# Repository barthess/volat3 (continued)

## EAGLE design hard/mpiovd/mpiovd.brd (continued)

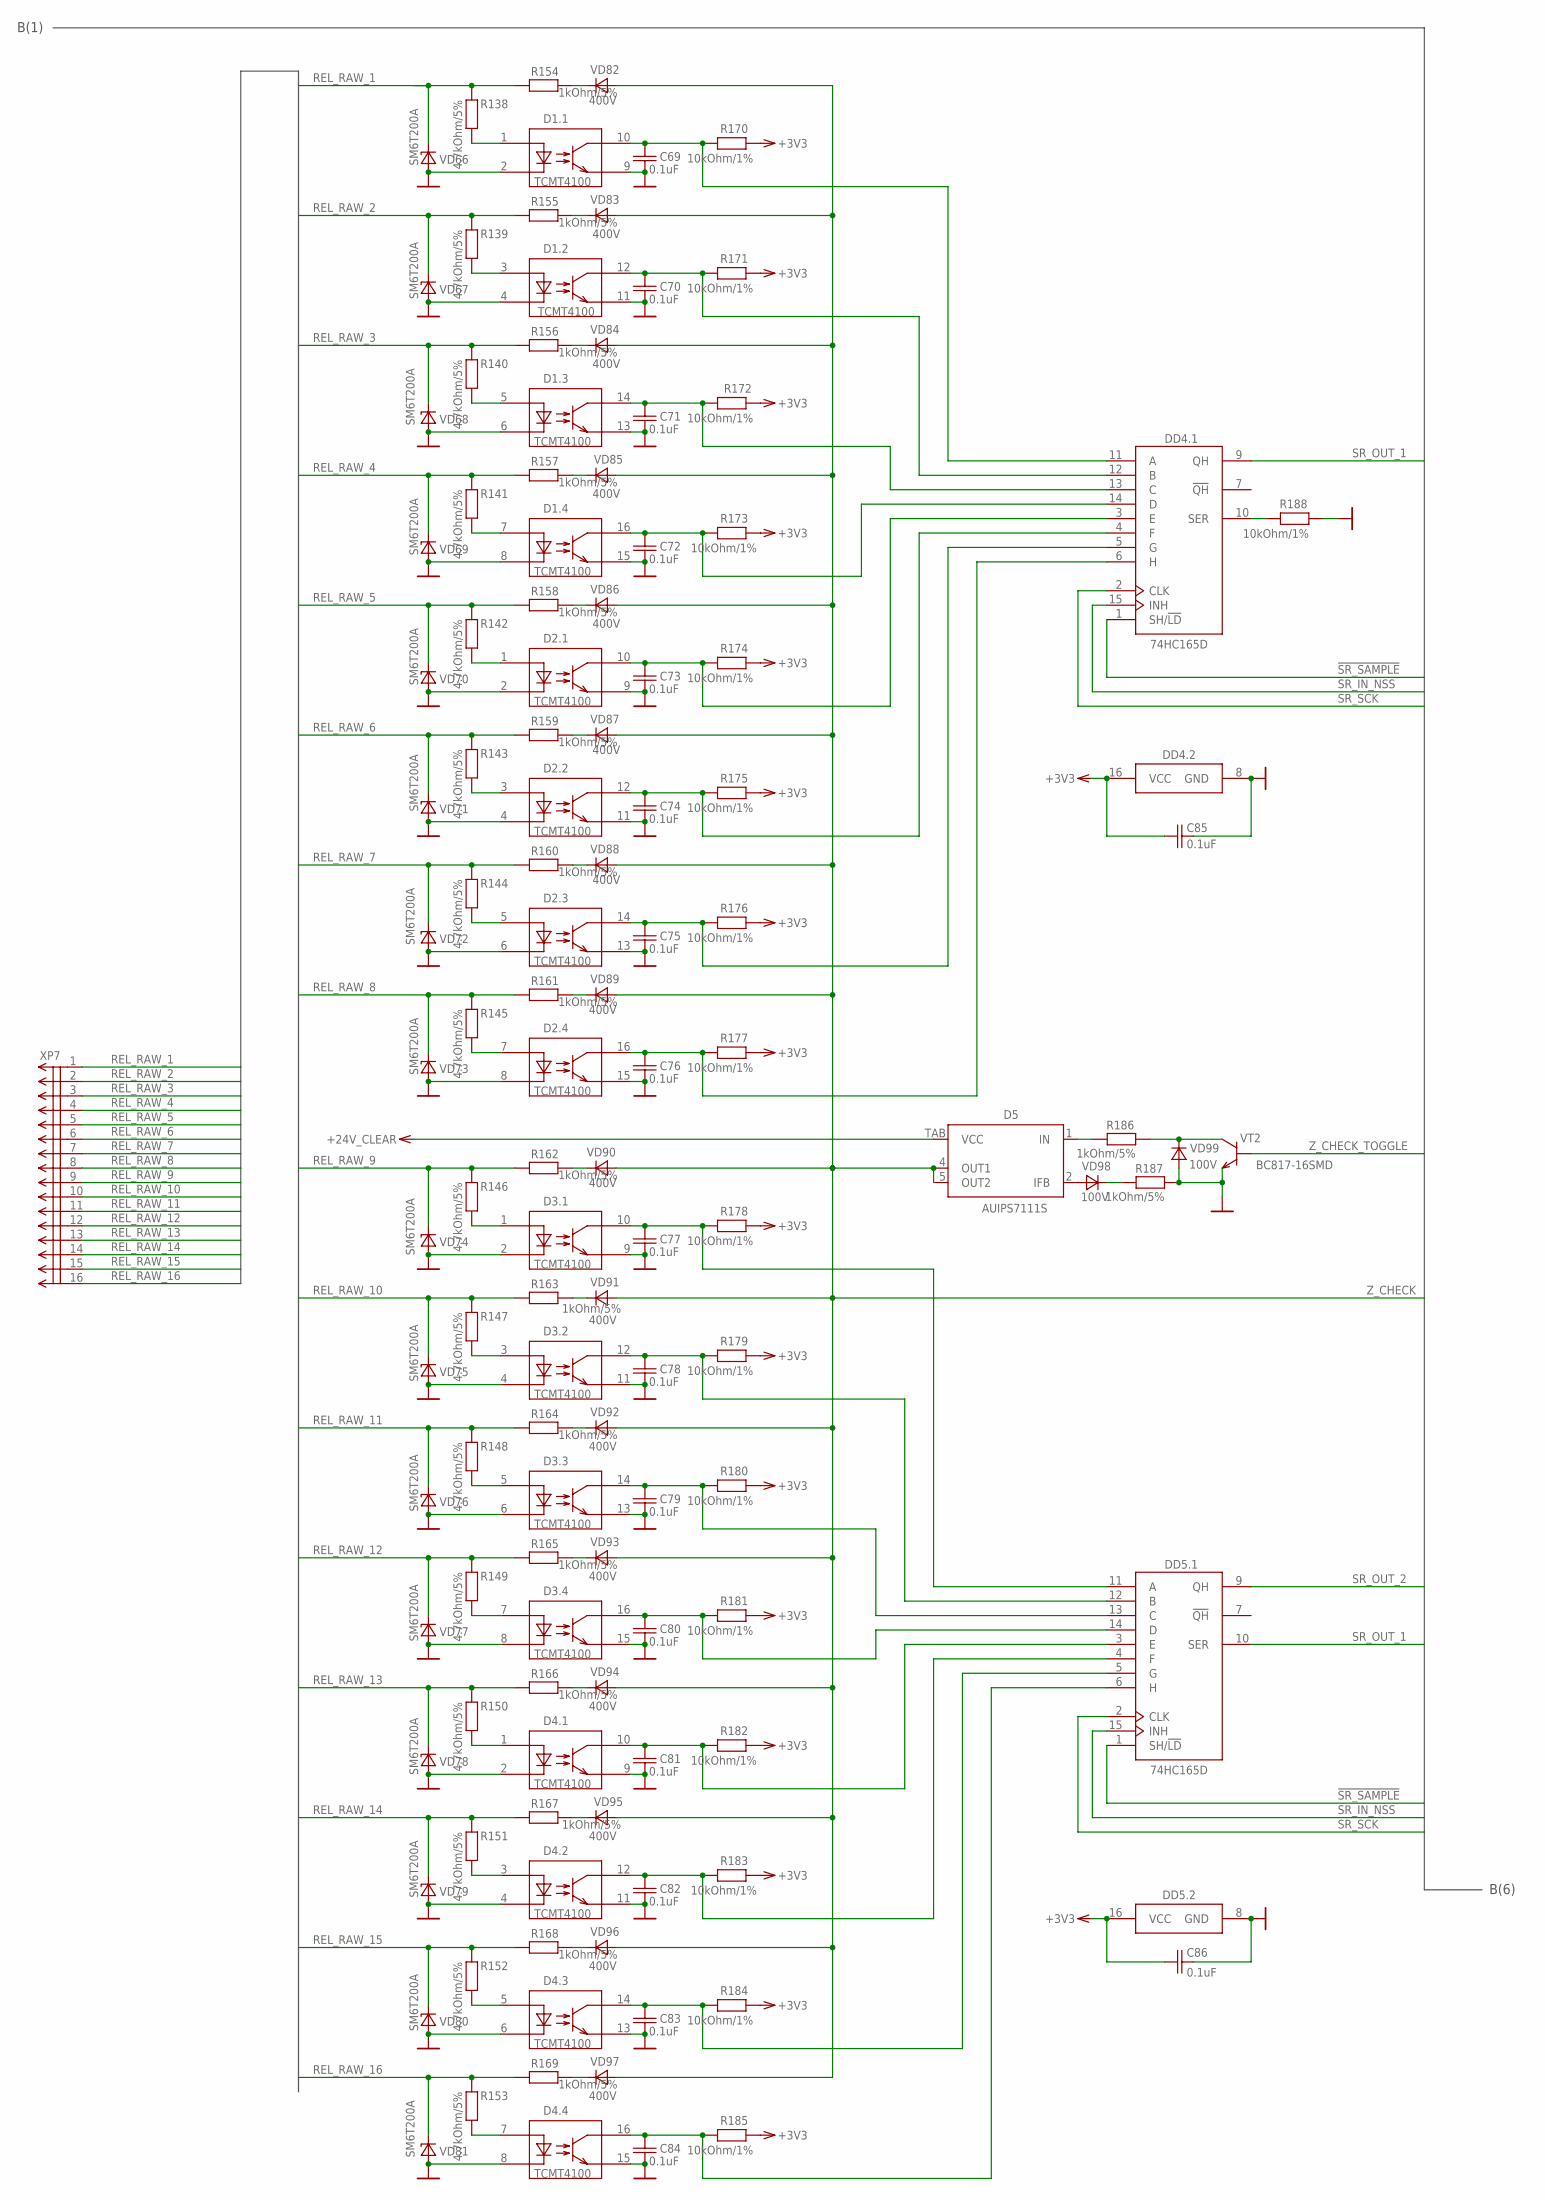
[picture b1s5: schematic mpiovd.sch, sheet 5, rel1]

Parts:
C69, C70, C71, C72, C73, C74, C75, C76, C77, C78, C79, C80, C81, C82, C83, C84, C85, C86: 0.1uF; C0603; PARTNO C0603C104K5RACTU
D1, D2, D3, D4: TCMT4100; SO16; PARTNO TCMT4100
D5: AUIPS7111S; TO252-5-11; PARTNO AUIPS7111S
DD4, DD5: 74HC165D; SO16; PARTNO IN74HC165AD
R138, R139, R140, R141, R142, R143, R144, R145, R146, R147, R148, R149, R150, R151, R152, R153: 4.7kOhm/5%; R1206; PARTNO RC1206JR-074K7L
R154, R155, R156, R157, R158, R159, R160, R161, R162, R163, R164, R165, R166, R167, R168, R169: 1kOhm/5%; R2512; PARTNO RC2512JK-071KL
R170, R171, R172, R173, R174, R175, R176, R177, R178, R179, R180, R181, R182, R183, R184, R185, R188: 10kOhm/1%; R0603; PARTNO RC0603FR-1010KL
R186, R187: 1kOhm/5%; R0805; PARTNO ERJ6GEYJ102V
VD66, VD67, VD68, VD69, VD70, VD71, VD72, VD73, VD74, VD75, VD76, VD77, VD78, VD79, VD80, VD81: SM6T200A; SMB; PARTNO SM6T200A
VD82, VD83, VD84, VD85, VD86, VD87, VD88, VD89, VD90, VD91, VD92, VD93, VD94, VD95, VD96, VD97: 400V; SMA; PARTNO S1G-E3/61T
VD98, VD99: 100V; SOD323; PARTNO 1N4148WS-V-GS18
VT2: BC817-16SMD; SOT23-BEC; PARTNO BC817
XP7: MOLEX-90130-16; PARTNO 90130-1216

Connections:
!SR_SAMPLE: DD4.1 (SH/!LD), DD5.1 (SH/!LD); also elsewhere on the board
+3V3: C85.1, C86.1, DD4.16 (VCC), DD5.16 (VCC), R170.1, R171.1, R172.1, R173.1, R174.1, R175.1, R176.1, R177.1, R178.1, R179.1, R180.1, R181.1, R182.1, R183.1, R184.1, R185.1; also elsewhere on the board
+24V_CLEAR: D5.TAB (VCC); also elsewhere on the board
DISCRETE_1: C69.1, D1.10 (TC), DD4.11 (A), R170.2
DISCRETE_2: C70.1, D1.12 (TC), DD4.12 (B), R171.2
DISCRETE_3: C71.1, D1.14 (TC), DD4.13 (C), R172.2
DISCRETE_4: C72.1, D1.16 (TC), DD4.14 (D), R173.2
DISCRETE_5: C73.1, D2.10 (TC), DD4.3 (E), R174.2
DISCRETE_6: C74.1, D2.12 (TC), DD4.4 (F), R175.2
DISCRETE_7: C75.1, D2.14 (TC), DD4.5 (G), R176.2
DISCRETE_8: C76.1, D2.16 (TC), DD4.6 (H), R177.2
DISCRETE_9: C77.1, D3.10 (TC), DD5.11 (A), R178.2
DISCRETE_10: C78.1, D3.12 (TC), DD5.12 (B), R179.2
DISCRETE_11: C79.1, D3.14 (TC), DD5.13 (C), R180.2
DISCRETE_12: C80.1, D3.16 (TC), DD5.14 (D), R181.2
DISCRETE_13: C81.1, D4.10 (TC), DD5.3 (E), R182.2
DISCRETE_14: C82.1, D4.12 (TC), DD5.4 (F), R183.2
DISCRETE_15: C83.1, D4.14 (TC), DD5.5 (G), R184.2
DISCRETE_16: C84.1, D4.16 (TC), DD5.6 (H), R185.2
GND: C69.2, C70.2, C71.2, C72.2, C73.2, C74.2, C75.2, C76.2, C77.2, C78.2, C79.2, C80.2, C81.2, C82.2, C83.2, C84.2, C85.2, C86.2, D1.2 (DC), D1.4 (DC), D1.6 (DC), D1.8 (DC), D1.9 (TE), D1.11 (TE), D1.13 (TE), D1.15 (TE), D2.2 (DC), D2.4 (DC), D2.6 (DC), D2.8 (DC), D2.9 (TE), D2.11 (TE), D2.13 (TE), D2.15 (TE), D3.2 (DC), D3.4 (DC), D3.6 (DC), D3.8 (DC), D3.9 (TE), D3.11 (TE), D3.13 (TE), D3.15 (TE), D4.2 (DC), D4.4 (DC), D4.6 (DC), D4.8 (DC), D4.9 (TE), D4.11 (TE), D4.13 (TE), D4.15 (TE), DD4.8 (GND), DD5.8 (GND), R187.1, R188.1, VD66.A, VD67.A, VD68.A, VD69.A, VD70.A, VD71.A, VD72.A, VD73.A, VD74.A, VD75.A, VD76.A, VD77.A, VD78.A, VD79.A, VD80.A, VD81.A, VD99.A, VT2.E; also elsewhere on the board
unnamed: D5.1 (IN), R186.2
unnamed: R186.1, VD99.C, VT2.C
unnamed: D5.2 (IFB), VD98.A
unnamed: R187.2, VD98.C
unnamed: R154.2, VD82.C
unnamed: R155.2, VD83.C
unnamed: R156.2, VD84.C
unnamed: R157.2, VD85.C
unnamed: R158.2, VD86.C
unnamed: R159.2, VD87.C
unnamed: R160.2, VD88.C
unnamed: R161.2, VD89.C
unnamed: R162.2, VD90.C
unnamed: R163.2, VD91.C
unnamed: R164.2, VD92.C
unnamed: R165.2, VD93.C
unnamed: R166.2, VD94.C
unnamed: R167.2, VD95.C
unnamed: R168.2, VD96.C
unnamed: R169.2, VD97.C
unnamed: D1.1 (DA), R138.2
unnamed: D1.3 (DA), R139.2
unnamed: D1.5 (DA), R140.2
unnamed: D1.7 (DA), R141.2
unnamed: D2.1 (DA), R142.2
unnamed: D2.3 (DA), R143.2
unnamed: D2.5 (DA), R144.2
unnamed: D2.7 (DA), R145.2
unnamed: D3.1 (DA), R146.2
unnamed: D3.3 (DA), R147.2
unnamed: D3.5 (DA), R148.2
unnamed: D3.7 (DA), R149.2
unnamed: D4.1 (DA), R150.2
unnamed: D4.3 (DA), R151.2
unnamed: D4.5 (DA), R152.2
unnamed: D4.7 (DA), R153.2
unnamed: DD4.10 (SER), R188.2
REL_RAW_1: R138.1, R154.1, VD66.C, XP7.1
REL_RAW_2: R139.1, R155.1, VD67.C, XP7.2
REL_RAW_3: R140.1, R156.1, VD68.C, XP7.3
REL_RAW_4: R141.1, R157.1, VD69.C, XP7.4
REL_RAW_5: R142.1, R158.1, VD70.C, XP7.5
REL_RAW_6: R143.1, R159.1, VD71.C, XP7.6
REL_RAW_7: R144.1, R160.1, VD72.C, XP7.7
REL_RAW_8: R145.1, R161.1, VD73.C, XP7.8
REL_RAW_9: R146.1, R162.1, VD74.C, XP7.9
REL_RAW_10: R147.1, R163.1, VD75.C, XP7.10
REL_RAW_11: R148.1, R164.1, VD76.C, XP7.11
REL_RAW_12: R149.1, R165.1, VD77.C, XP7.12
REL_RAW_13: R150.1, R166.1, VD78.C, XP7.13
REL_RAW_14: R151.1, R167.1, VD79.C, XP7.14
REL_RAW_15: R152.1, R168.1, VD80.C, XP7.15
REL_RAW_16: R153.1, R169.1, VD81.C, XP7.16
SR_IN_NSS: DD4.15 (INH), DD5.15 (INH); also elsewhere on the board
SR_OUT_1: DD4.9 (QH), DD5.10 (SER)
SR_OUT_2: DD5.9 (QH); also elsewhere on the board
SR_SCK: DD4.2 (CLK), DD5.2 (CLK); also elsewhere on the board
Z_CHECK: D5.4 (OUT1), D5.5 (OUT2), VD82.A, VD83.A, VD84.A, VD85.A, VD86.A, VD87.A, VD88.A, VD89.A, VD90.A, VD91.A, VD92.A, VD93.A, VD94.A, VD95.A, VD96.A, VD97.A; also elsewhere on the board
Z_CHECK_TOGGLE: VT2.B; also elsewhere on the board

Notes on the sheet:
B(6)
B(1)

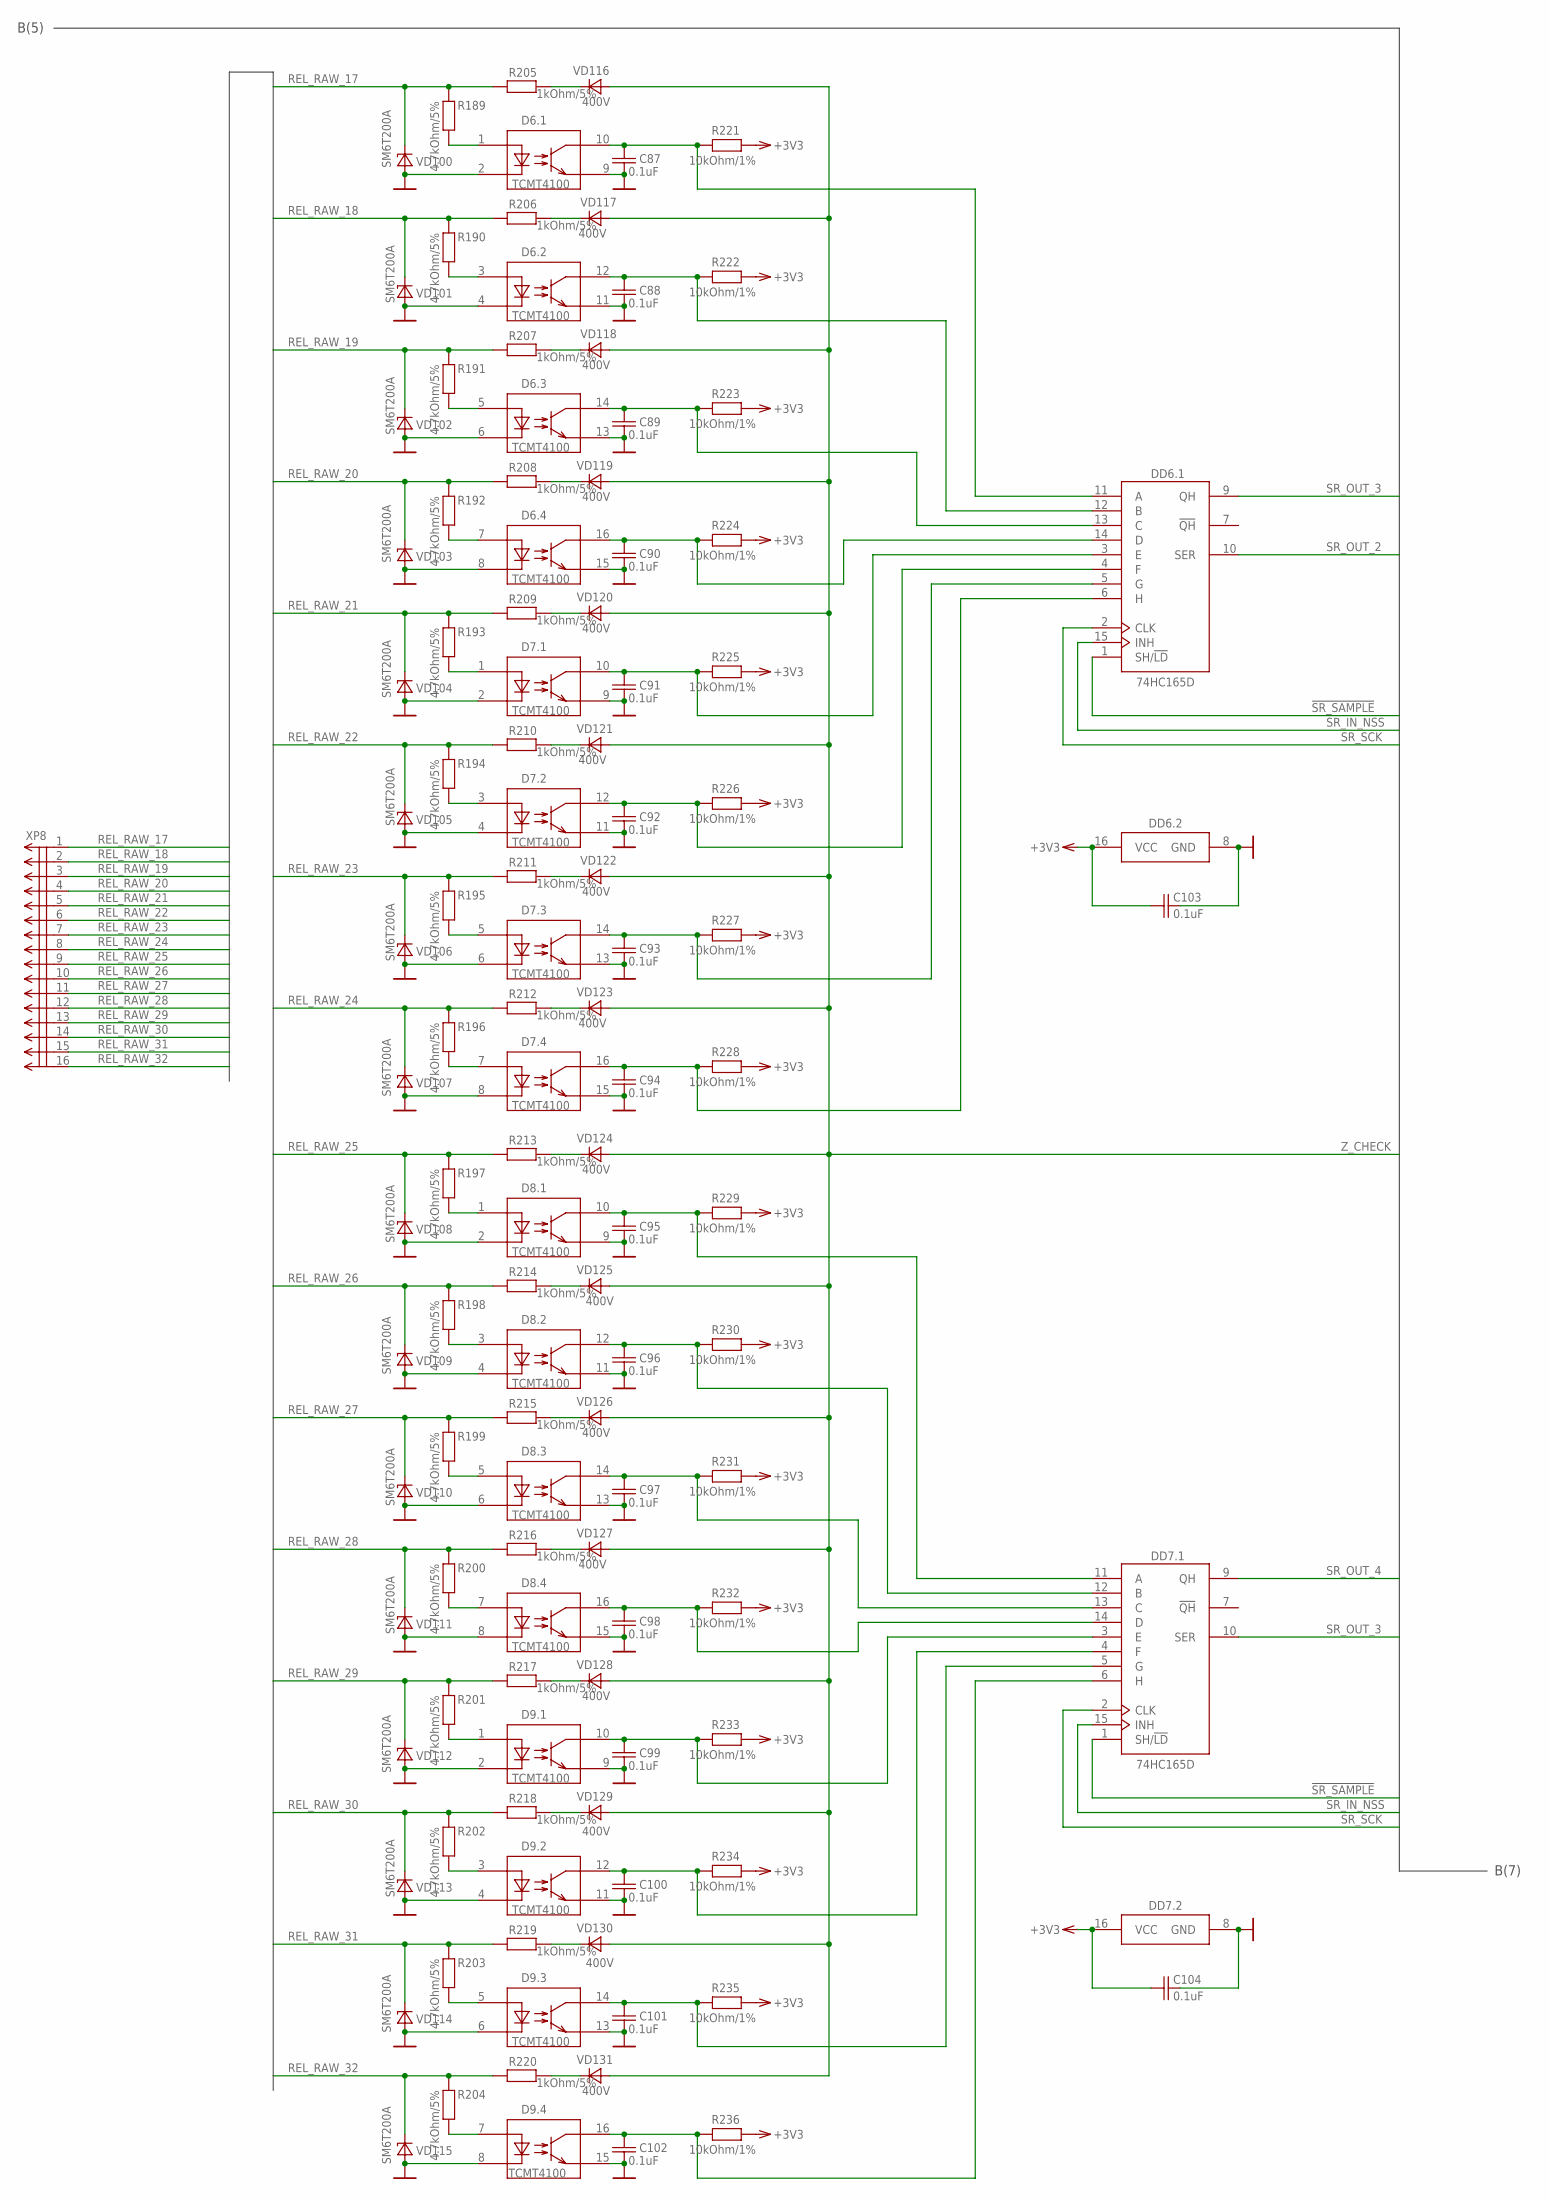
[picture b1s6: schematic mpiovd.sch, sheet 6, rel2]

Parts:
C87, C88, C89, C90, C91, C92, C93, C94, C95, C96, C97, C98, C99, C100, C101, C102, C103, C104: 0.1uF; C0603; PARTNO C0603C104K5RACTU
D6, D7, D8, D9: TCMT4100; SO16; PARTNO TCMT4100
DD6, DD7: 74HC165D; SO16; PARTNO IN74HC165AD
R189, R190, R191, R192, R193, R194, R195, R196, R197, R198, R199, R200, R201, R202, R203, R204: 4.7kOhm/5%; R1206; PARTNO RC1206JR-074K7L
R205, R206, R207, R208, R209, R210, R211, R212, R213, R214, R215, R216, R217, R218, R219, R220: 1kOhm/5%; R2512; PARTNO RC2512JK-071KL
R221, R222, R223, R224, R225, R226, R227, R228, R229, R230, R231, R232, R233, R234, R235, R236: 10kOhm/1%; R0603; PARTNO RC0603FR-1010KL
VD100, VD101, VD102, VD103, VD104, VD105, VD106, VD107, VD108, VD109, VD110, VD111, VD112, VD113, VD114, VD115: SM6T200A; SMB; PARTNO SM6T200A
VD116, VD117, VD118, VD119, VD120, VD121, VD122, VD123, VD124, VD125, VD126, VD127, VD128, VD129, VD130, VD131: 400V; SMA; PARTNO S1G-E3/61T
XP8: MOLEX-90130-16; PARTNO 90130-1216

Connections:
!SR_SAMPLE: DD6.1 (SH/!LD), DD7.1 (SH/!LD); also elsewhere on the board
+3V3: C103.1, C104.1, DD6.16 (VCC), DD7.16 (VCC), R221.1, R222.1, R223.1, R224.1, R225.1, R226.1, R227.1, R228.1, R229.1, R230.1, R231.1, R232.1, R233.1, R234.1, R235.1, R236.1; also elsewhere on the board
DISCRETE_17: C87.1, D6.10 (TC), DD6.11 (A), R221.2
DISCRETE_18: C88.1, D6.12 (TC), DD6.12 (B), R222.2
DISCRETE_19: C89.1, D6.14 (TC), DD6.13 (C), R223.2
DISCRETE_20: C90.1, D6.16 (TC), DD6.14 (D), R224.2
DISCRETE_21: C91.1, D7.10 (TC), DD6.3 (E), R225.2
DISCRETE_22: C92.1, D7.12 (TC), DD6.4 (F), R226.2
DISCRETE_23: C93.1, D7.14 (TC), DD6.5 (G), R227.2
DISCRETE_24: C94.1, D7.16 (TC), DD6.6 (H), R228.2
DISCRETE_25: C95.1, D8.10 (TC), DD7.11 (A), R229.2
DISCRETE_26: C96.1, D8.12 (TC), DD7.12 (B), R230.2
DISCRETE_27: C97.1, D8.14 (TC), DD7.13 (C), R231.2
DISCRETE_28: C98.1, D8.16 (TC), DD7.14 (D), R232.2
DISCRETE_29: C99.1, D9.10 (TC), DD7.3 (E), R233.2
DISCRETE_30: C100.1, D9.12 (TC), DD7.4 (F), R234.2
DISCRETE_31: C101.1, D9.14 (TC), DD7.5 (G), R235.2
DISCRETE_32: C102.1, D9.16 (TC), DD7.6 (H), R236.2
GND: C87.2, C88.2, C89.2, C90.2, C91.2, C92.2, C93.2, C94.2, C95.2, C96.2, C97.2, C98.2, C99.2, C100.2, C101.2, C102.2, C103.2, C104.2, D6.2 (DC), D6.4 (DC), D6.6 (DC), D6.8 (DC), D6.9 (TE), D6.11 (TE), D6.13 (TE), D6.15 (TE), D7.2 (DC), D7.4 (DC), D7.6 (DC), D7.8 (DC), D7.9 (TE), D7.11 (TE), D7.13 (TE), D7.15 (TE), D8.2 (DC), D8.4 (DC), D8.6 (DC), D8.8 (DC), D8.9 (TE), D8.11 (TE), D8.13 (TE), D8.15 (TE), D9.2 (DC), D9.4 (DC), D9.6 (DC), D9.8 (DC), D9.9 (TE), D9.11 (TE), D9.13 (TE), D9.15 (TE), DD6.8 (GND), DD7.8 (GND), VD100.A, VD101.A, VD102.A, VD103.A, VD104.A, VD105.A, VD106.A, VD107.A, VD108.A, VD109.A, VD110.A, VD111.A, VD112.A, VD113.A, VD114.A, VD115.A; also elsewhere on the board
unnamed: R205.2, VD116.C
unnamed: R206.2, VD117.C
unnamed: R207.2, VD118.C
unnamed: R208.2, VD119.C
unnamed: R209.2, VD120.C
unnamed: R210.2, VD121.C
unnamed: R211.2, VD122.C
unnamed: R212.2, VD123.C
unnamed: R213.2, VD124.C
unnamed: R214.2, VD125.C
unnamed: R215.2, VD126.C
unnamed: R216.2, VD127.C
unnamed: R217.2, VD128.C
unnamed: R218.2, VD129.C
unnamed: R219.2, VD130.C
unnamed: R220.2, VD131.C
unnamed: D6.1 (DA), R189.2
unnamed: D6.3 (DA), R190.2
unnamed: D6.5 (DA), R191.2
unnamed: D6.7 (DA), R192.2
unnamed: D7.1 (DA), R193.2
unnamed: D7.3 (DA), R194.2
unnamed: D7.5 (DA), R195.2
unnamed: D7.7 (DA), R196.2
unnamed: D8.1 (DA), R197.2
unnamed: D8.3 (DA), R198.2
unnamed: D8.5 (DA), R199.2
unnamed: D8.7 (DA), R200.2
unnamed: D9.1 (DA), R201.2
unnamed: D9.3 (DA), R202.2
unnamed: D9.5 (DA), R203.2
unnamed: D9.7 (DA), R204.2
REL_RAW_17: R189.1, R205.1, VD100.C, XP8.1
REL_RAW_18: R190.1, R206.1, VD101.C, XP8.2
REL_RAW_19: R191.1, R207.1, VD102.C, XP8.3
REL_RAW_20: R192.1, R208.1, VD103.C, XP8.4
REL_RAW_21: R193.1, R209.1, VD104.C, XP8.5
REL_RAW_22: R194.1, R210.1, VD105.C, XP8.6
REL_RAW_23: R195.1, R211.1, VD106.C, XP8.7
REL_RAW_24: R196.1, R212.1, VD107.C, XP8.8
REL_RAW_25: R197.1, R213.1, VD108.C, XP8.9
REL_RAW_26: R198.1, R214.1, VD109.C, XP8.10
REL_RAW_27: R199.1, R215.1, VD110.C, XP8.11
REL_RAW_28: R200.1, R216.1, VD111.C, XP8.12
REL_RAW_29: R201.1, R217.1, VD112.C, XP8.13
REL_RAW_30: R202.1, R218.1, VD113.C, XP8.14
REL_RAW_31: R203.1, R219.1, VD114.C, XP8.15
REL_RAW_32: R204.1, R220.1, VD115.C, XP8.16
SR_IN_NSS: DD6.15 (INH), DD7.15 (INH); also elsewhere on the board
SR_OUT_2: DD6.10 (SER); also elsewhere on the board
SR_OUT_3: DD6.9 (QH), DD7.10 (SER)
SR_OUT_4: DD7.9 (QH); also elsewhere on the board
SR_SCK: DD6.2 (CLK), DD7.2 (CLK); also elsewhere on the board
Z_CHECK: VD116.A, VD117.A, VD118.A, VD119.A, VD120.A, VD121.A, VD122.A, VD123.A, VD124.A, VD125.A, VD126.A, VD127.A, VD128.A, VD129.A, VD130.A, VD131.A; also elsewhere on the board

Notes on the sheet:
B(5)
B(7)

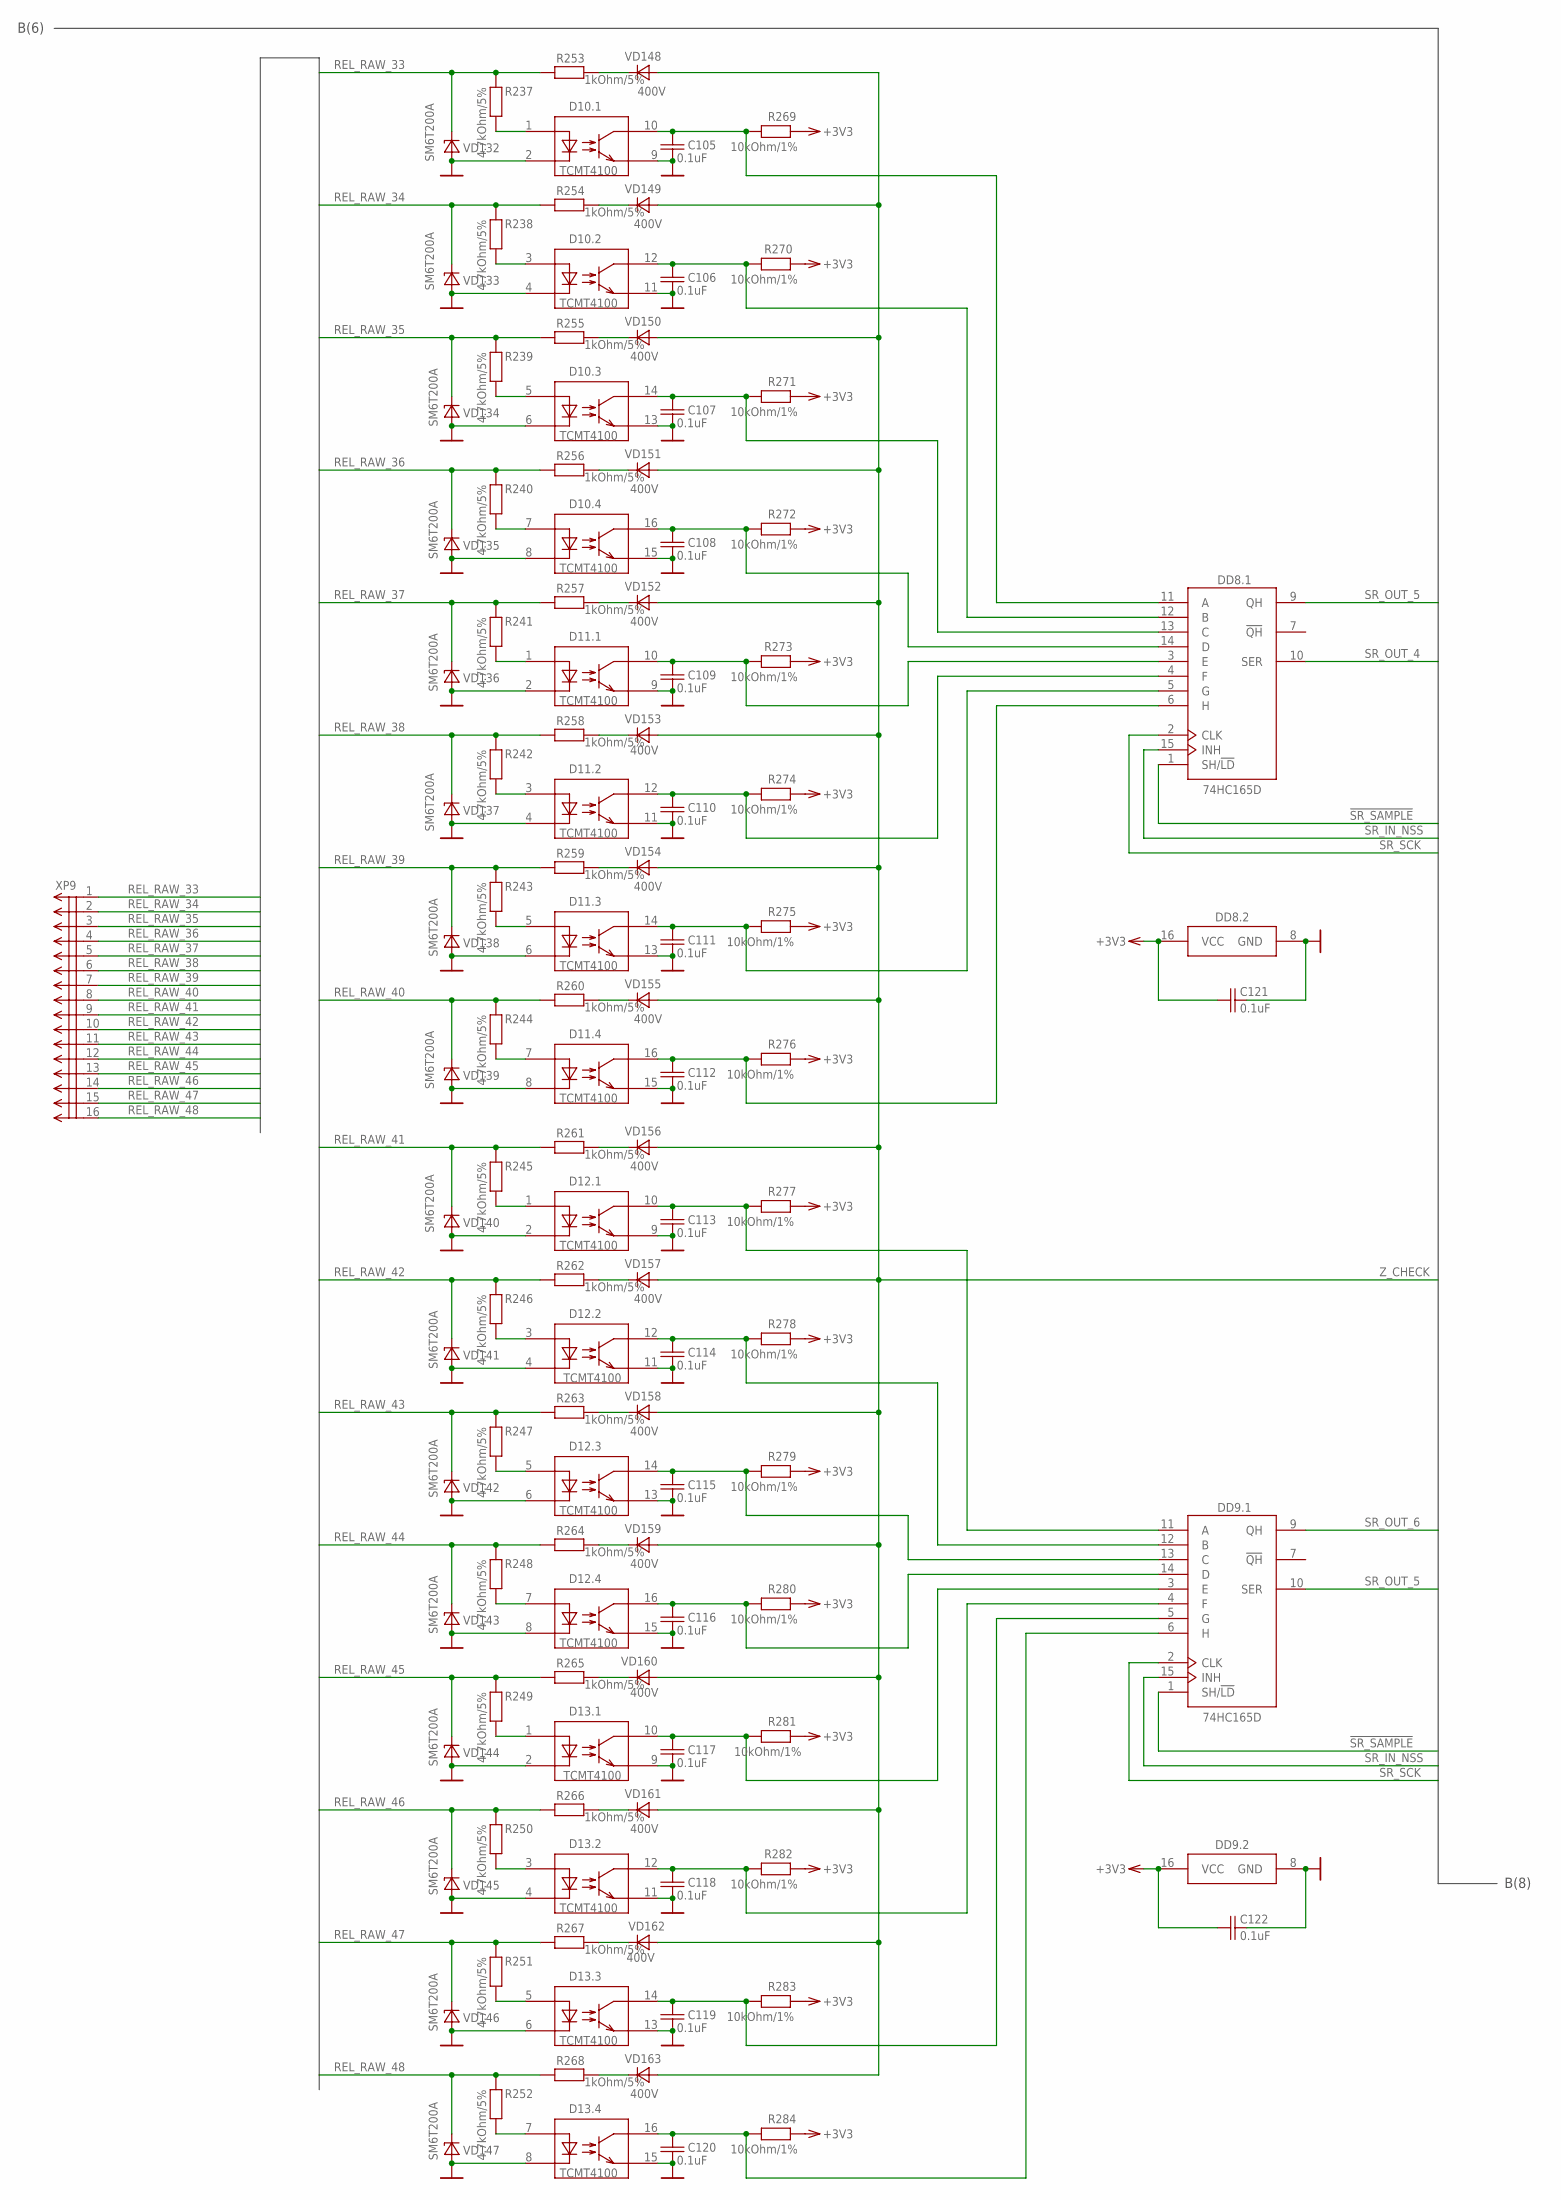
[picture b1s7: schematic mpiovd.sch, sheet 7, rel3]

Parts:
C105, C106, C107, C108, C109, C110, C111, C112, C113, C114, C115, C116, C117, C118, C119, C120, C121, C122: 0.1uF; C0603; PARTNO C0603C104K5RACTU
D10, D11, D12, D13: TCMT4100; SO16; PARTNO TCMT4100
DD8, DD9: 74HC165D; SO16; PARTNO IN74HC165AD
R237, R238, R239, R240, R241, R242, R243, R244, R245, R246, R247, R248, R249, R250, R251, R252: 4.7kOhm/5%; R1206; PARTNO RC1206JR-074K7L
R253, R254, R255, R256, R257, R258, R259, R260, R261, R262, R263, R264, R265, R266, R267, R268: 1kOhm/5%; R2512; PARTNO RC2512JK-071KL
R269, R270, R271, R272, R273, R274, R275, R276, R277, R278, R279, R280, R281, R282, R283, R284: 10kOhm/1%; R0603; PARTNO RC0603FR-1010KL
VD132, VD133, VD134, VD135, VD136, VD137, VD138, VD139, VD140, VD141, VD142, VD143, VD144, VD145, VD146, VD147: SM6T200A; SMB; PARTNO SM6T200A
VD148, VD149, VD150, VD151, VD152, VD153, VD154, VD155, VD156, VD157, VD158, VD159, VD160, VD161, VD162, VD163: 400V; SMA; PARTNO S1G-E3/61T
XP9: MOLEX-90130-16; PARTNO 90130-1216

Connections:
!SR_SAMPLE: DD8.1 (SH/!LD), DD9.1 (SH/!LD); also elsewhere on the board
+3V3: C121.1, C122.1, DD8.16 (VCC), DD9.16 (VCC), R269.1, R270.1, R271.1, R272.1, R273.1, R274.1, R275.1, R276.1, R277.1, R278.1, R279.1, R280.1, R281.1, R282.1, R283.1, R284.1; also elsewhere on the board
DISCRETE_33: C105.1, D10.10 (TC), DD8.11 (A), R269.2
DISCRETE_34: C106.1, D10.12 (TC), DD8.12 (B), R270.2
DISCRETE_35: C107.1, D10.14 (TC), DD8.13 (C), R271.2
DISCRETE_36: C108.1, D10.16 (TC), DD8.14 (D), R272.2
DISCRETE_37: C109.1, D11.10 (TC), DD8.3 (E), R273.2
DISCRETE_38: C110.1, D11.12 (TC), DD8.4 (F), R274.2
DISCRETE_39: C111.1, D11.14 (TC), DD8.5 (G), R275.2
DISCRETE_40: C112.1, D11.16 (TC), DD8.6 (H), R276.2
DISCRETE_41: C113.1, D12.10 (TC), DD9.11 (A), R277.2
DISCRETE_42: C114.1, D12.12 (TC), DD9.12 (B), R278.2
DISCRETE_43: C115.1, D12.14 (TC), DD9.13 (C), R279.2
DISCRETE_44: C116.1, D12.16 (TC), DD9.14 (D), R280.2
DISCRETE_45: C117.1, D13.10 (TC), DD9.3 (E), R281.2
DISCRETE_46: C118.1, D13.12 (TC), DD9.4 (F), R282.2
DISCRETE_47: C119.1, D13.14 (TC), DD9.5 (G), R283.2
DISCRETE_48: C120.1, D13.16 (TC), DD9.6 (H), R284.2
GND: C105.2, C106.2, C107.2, C108.2, C109.2, C110.2, C111.2, C112.2, C113.2, C114.2, C115.2, C116.2, C117.2, C118.2, C119.2, C120.2, C121.2, C122.2, D10.2 (DC), D10.4 (DC), D10.6 (DC), D10.8 (DC), D10.9 (TE), D10.11 (TE), D10.13 (TE), D10.15 (TE), D11.2 (DC), D11.4 (DC), D11.6 (DC), D11.8 (DC), D11.9 (TE), D11.11 (TE), D11.13 (TE), D11.15 (TE), D12.2 (DC), D12.4 (DC), D12.6 (DC), D12.8 (DC), D12.9 (TE), D12.11 (TE), D12.13 (TE), D12.15 (TE), D13.2 (DC), D13.4 (DC), D13.6 (DC), D13.8 (DC), D13.9 (TE), D13.11 (TE), D13.13 (TE), D13.15 (TE), DD8.8 (GND), DD9.8 (GND), VD132.A, VD133.A, VD134.A, VD135.A, VD136.A, VD137.A, VD138.A, VD139.A, VD140.A, VD141.A, VD142.A, VD143.A, VD144.A, VD145.A, VD146.A, VD147.A; also elsewhere on the board
unnamed: D10.1 (DA), R237.2
unnamed: D10.3 (DA), R238.2
unnamed: D10.5 (DA), R239.2
unnamed: D10.7 (DA), R240.2
unnamed: R253.2, VD148.C
unnamed: D11.1 (DA), R241.2
unnamed: D11.3 (DA), R242.2
unnamed: D11.5 (DA), R243.2
unnamed: D11.7 (DA), R244.2
unnamed: D12.1 (DA), R245.2
unnamed: D12.3 (DA), R246.2
unnamed: D12.5 (DA), R247.2
unnamed: D12.7 (DA), R248.2
unnamed: D13.1 (DA), R249.2
unnamed: D13.3 (DA), R250.2
unnamed: D13.5 (DA), R251.2
unnamed: D13.7 (DA), R252.2
unnamed: R254.2, VD149.C
unnamed: R255.2, VD150.C
unnamed: R256.2, VD151.C
unnamed: R257.2, VD152.C
unnamed: R258.2, VD153.C
unnamed: R259.2, VD154.C
unnamed: R260.2, VD155.C
unnamed: R261.2, VD156.C
unnamed: R262.2, VD157.C
unnamed: R263.2, VD158.C
unnamed: R264.2, VD159.C
unnamed: R265.2, VD160.C
unnamed: R266.2, VD161.C
unnamed: R267.2, VD162.C
unnamed: R268.2, VD163.C
REL_RAW_33: R237.1, R253.1, VD132.C, XP9.1
REL_RAW_34: R238.1, R254.1, VD133.C, XP9.2
REL_RAW_35: R239.1, R255.1, VD134.C, XP9.3
REL_RAW_36: R240.1, R256.1, VD135.C, XP9.4
REL_RAW_37: R241.1, R257.1, VD136.C, XP9.5
REL_RAW_38: R242.1, R258.1, VD137.C, XP9.6
REL_RAW_39: R243.1, R259.1, VD138.C, XP9.7
REL_RAW_40: R244.1, R260.1, VD139.C, XP9.8
REL_RAW_41: R245.1, R261.1, VD140.C, XP9.9
REL_RAW_42: R246.1, R262.1, VD141.C, XP9.10
REL_RAW_43: R247.1, R263.1, VD142.C, XP9.11
REL_RAW_44: R248.1, R264.1, VD143.C, XP9.12
REL_RAW_45: R249.1, R265.1, VD144.C, XP9.13
REL_RAW_46: R250.1, R266.1, VD145.C, XP9.14
REL_RAW_47: R251.1, R267.1, VD146.C, XP9.15
REL_RAW_48: R252.1, R268.1, VD147.C, XP9.16
SR_IN_NSS: DD8.15 (INH), DD9.15 (INH); also elsewhere on the board
SR_OUT_4: DD8.10 (SER); also elsewhere on the board
SR_OUT_5: DD8.9 (QH), DD9.10 (SER)
SR_OUT_6: DD9.9 (QH); also elsewhere on the board
SR_SCK: DD8.2 (CLK), DD9.2 (CLK); also elsewhere on the board
Z_CHECK: VD148.A, VD149.A, VD150.A, VD151.A, VD152.A, VD153.A, VD154.A, VD155.A, VD156.A, VD157.A, VD158.A, VD159.A, VD160.A, VD161.A, VD162.A, VD163.A; also elsewhere on the board

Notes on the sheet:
B(8)
B(6)
